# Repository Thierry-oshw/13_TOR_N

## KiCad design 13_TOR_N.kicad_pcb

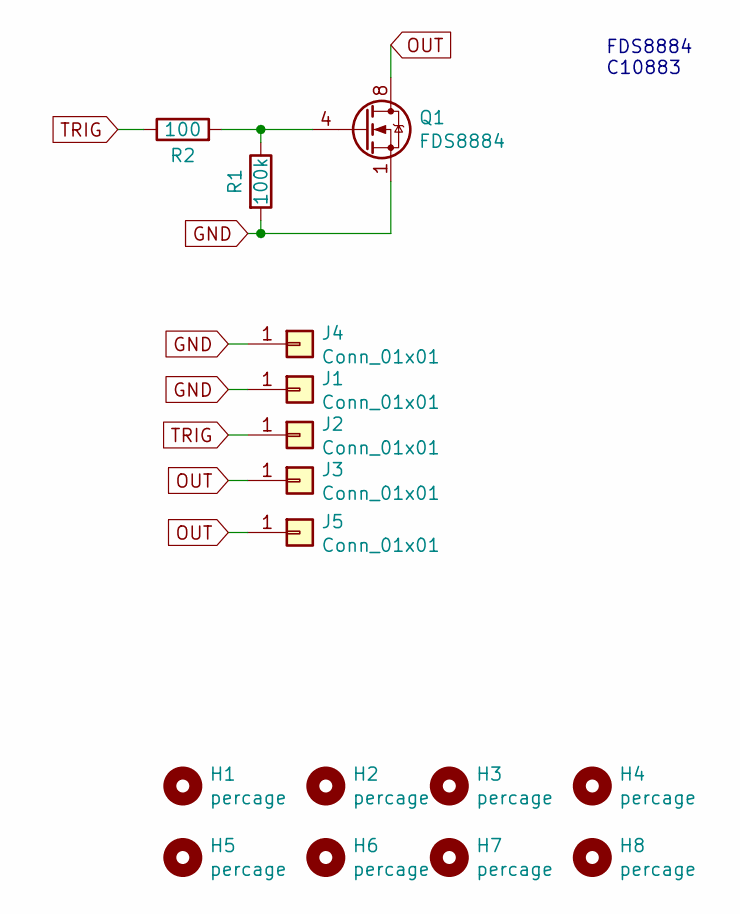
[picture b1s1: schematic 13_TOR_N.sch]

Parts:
H1, H2, H3, H4, H5, H6, H7, H8: percage; trou
J1, J2, J3, J4, J5: Conn_01x01; Castellated_conn
Q1: FDS8884; SOIC-8_3.9x4.9mm_P1.27mm
R1: 100k; R_0603_1608Metric_Pad1.05x0.95mm_HandSolder
R2: 100; R_0603_1608Metric_Pad1.05x0.95mm_HandSolder

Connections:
GND: J1.1, J4.1, Q1.1 (S), Q1.2 (S), Q1.3 (S), R1.2
unnamed: Q1.4 (G), R1.1, R2.2
OUT: J3.1, J5.1, Q1.5 (D), Q1.6 (D), Q1.7 (D), Q1.8 (D)
TRIG: J2.1, R2.1

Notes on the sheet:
FDS8884 C10883

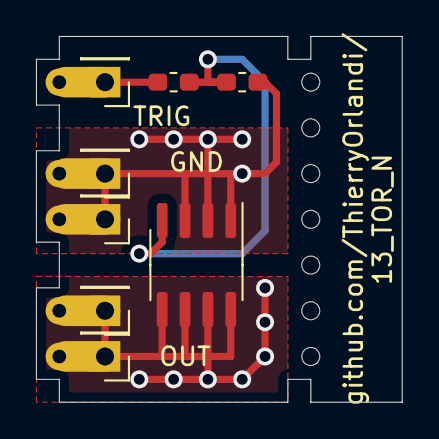
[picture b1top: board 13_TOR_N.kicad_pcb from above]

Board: 2 copper layers, 20.3 x 20.3 mm, 15 parts (0 on the bottom side), 4 nets.

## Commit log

2021-04-15 schema + placement + routage
2021-07-26 maj split librairies
2023-05-02 chgt nom fichier licence
